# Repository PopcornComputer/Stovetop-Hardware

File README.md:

# Stovetop Hardware
[![CC BY-NC-SA 4.0][cc-by-nc-sa-shield]][cc-by-nc-sa]
[![Follow Source Parts on Twitter][twitter-follow-shield]][twitter-follow]
[![Subscribe to Source Parts' Subreddit][reddit-subscribers-shield]][sourceparts-subreddit]

## Purchase
**Stovetop™** is available for purchase in our webstore: [https://shop.popcorncomputer.com/products/stovetop][webstore]

## Documentation
To view the documentation for **Stovetop™** please visit: [https://docs.popcorncomputer.com/Stovetop][stovetop-docs]

If you have done something cool with **Stovetop™** or feel that something is missing from the documentation, please feel free to open an issue in the [documentation repository][documentation-repo] or submit a Pull Request in that repository. The source files for our documentation website can be found in the /docs folder in the [documentation repository][documentation-repo].

## License & Copyright
This work is licensed under a
[Creative Commons Attribution-NonCommercial-ShareAlike 4.0 International License][cc-by-nc-sa].

[![CC BY-NC-SA 4.0][cc-by-nc-sa-image]][cc-by-nc-sa]

Source Parts Inc. © 2022

**Stovetop™** is a trademark of Source Parts Inc.

[cc-by-nc-sa]: http://creativecommons.org/licenses/by-nc-sa/4.0/
[cc-by-nc-sa-image]: https://licensebuttons.net/l/by-nc-sa/4.0/88x31.png
[cc-by-nc-sa-shield]: https://img.shields.io/badge/License-CC%20BY--NC--SA%204.0-lightgrey.svg
[twitter-follow]: https://twitter.com/intent/follow?screen_name=sourceparts
[twitter-follow-shield]: https://img.shields.io/twitter/follow/sourceparts?style=social&logo=twitter
[sourceparts-subreddit]: https://reddit.com/r/sourceparts
[reddit-subscribers-shield]: https://img.shields.io/reddit/subreddit-subscribers/sourceparts?style=social
[stovetop-docs]: https://docs.popcorncomputer.com/Stovetop
[webstore]: https://shop.popcorncomputer.com/products/stovetop
[documentation-repo]: https://github.com/PopcornComputer/Stovetop

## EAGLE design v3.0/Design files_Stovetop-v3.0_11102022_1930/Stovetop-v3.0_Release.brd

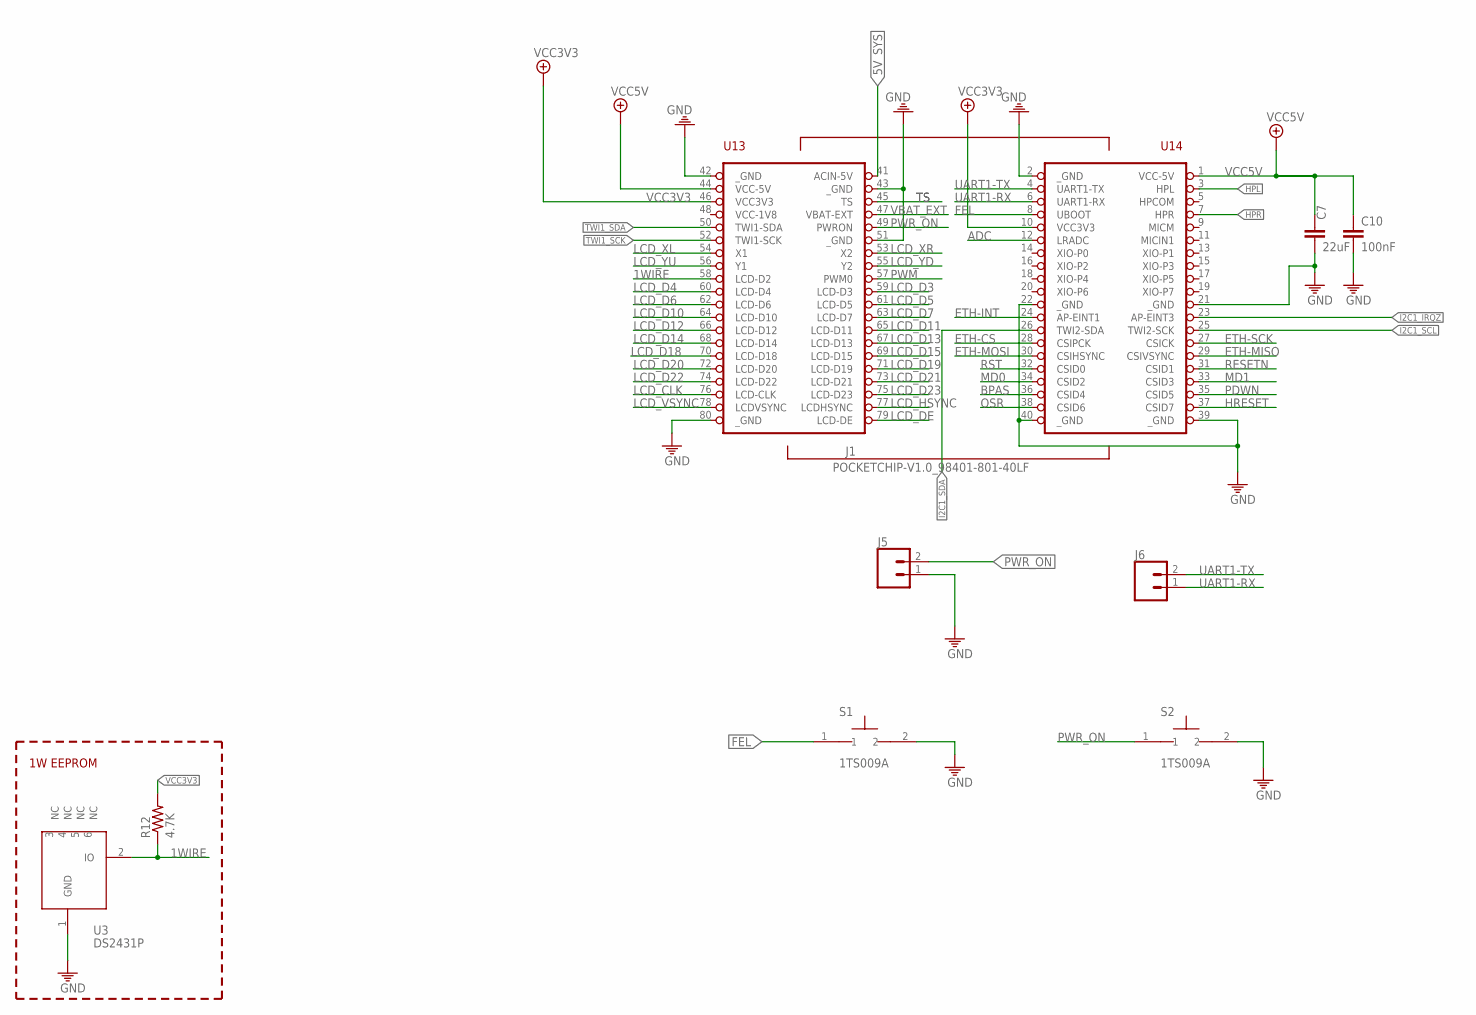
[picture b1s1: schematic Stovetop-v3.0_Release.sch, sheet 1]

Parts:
C7: 22uF; C1206
C10: 100nF; C0402
J1: POCKETCHIP-V1.0_98401-801-40LF
J5, J6: CONN_02LOCK; 1X02_LOCK
R12: 4.7K; R0402
S1, S2: 1TS009A
U3: DS2431P; TSOC6

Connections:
1WIRE: J1.58 (LCD-D2), R12.1, U3.2 (IO)
5V_SYS: J1.41 (ACIN-5V); also elsewhere on the board
ADC: J1.12 (LRADC)
BPAS: J1.36 (CSID4); also elsewhere on the board
ETH-CS: J1.28 (CSIPCK); also elsewhere on the board
ETH-INT: J1.24 (AP-EINT1); also elsewhere on the board
ETH-MISO: J1.29 (CSIVSYNC); also elsewhere on the board
ETH-MOSI: J1.30 (CSIHSYNC); also elsewhere on the board
ETH-SCK: J1.27 (CSICK); also elsewhere on the board
FEL: J1.8 (UBOOT), S1.1
GND: C7.2, C10.2, J1.2 (_GND), J1.21 (_GND), J1.22 (_GND), J1.39 (_GND), J1.40 (_GND), J1.42 (_GND), J1.43 (_GND), J1.51 (_GND), J1.80 (_GND), J5.1, S1.2, S2.2, U3.1 (GND); also elsewhere on the board
HPL: J1.3 (HPL); also elsewhere on the board
HPR: J1.7 (HPR); also elsewhere on the board
HRESET: J1.37 (CSID7); also elsewhere on the board
I2C1_IRQZ: J1.23 (AP-EINT3); also elsewhere on the board
I2C1_SCL: J1.25 (TWI2-SCK); also elsewhere on the board
I2C1_SDA: J1.26 (TWI2-SDA); also elsewhere on the board
LCD_CLK: J1.76 (LCD-CLK); also elsewhere on the board
LCD_D3: J1.59 (LCD-D3); also elsewhere on the board
LCD_D4: J1.60 (LCD-D4); also elsewhere on the board
LCD_D5: J1.61 (LCD-D5); also elsewhere on the board
LCD_D6: J1.62 (LCD-D6); also elsewhere on the board
LCD_D7: J1.63 (LCD-D7); also elsewhere on the board
LCD_D10: J1.64 (LCD-D10); also elsewhere on the board
LCD_D11: J1.65 (LCD-D11); also elsewhere on the board
LCD_D12: J1.66 (LCD-D12); also elsewhere on the board
LCD_D13: J1.67 (LCD-D13); also elsewhere on the board
LCD_D14: J1.68 (LCD-D14); also elsewhere on the board
LCD_D15: J1.69 (LCD-D15); also elsewhere on the board
LCD_D18: J1.70 (LCD-D18); also elsewhere on the board
LCD_D19: J1.71 (LCD-D19); also elsewhere on the board
LCD_D20: J1.72 (LCD-D20); also elsewhere on the board
LCD_D21: J1.73 (LCD-D21); also elsewhere on the board
LCD_D22: J1.74 (LCD-D22); also elsewhere on the board
LCD_D23: J1.75 (LCD-D23); also elsewhere on the board
LCD_DE: J1.79 (LCD-DE); also elsewhere on the board
LCD_HSYNC: J1.77 (LCDHSYNC); also elsewhere on the board
LCD_VSYNC: J1.78 (LCDVSYNC); also elsewhere on the board
LCD_XL: J1.54 (X1)
LCD_XR: J1.53 (X2)
LCD_YD: J1.55 (Y2)
LCD_YU: J1.56 (Y1)
MD0: J1.34 (CSID2); also elsewhere on the board
MD1: J1.33 (CSID3); also elsewhere on the board
OSR: J1.38 (CSID6); also elsewhere on the board
PDWN: J1.35 (CSID5); also elsewhere on the board
PWM: J1.57 (PWM0)
PWR_ON: J1.49 (PWRON), J5.2, S2.1
RESETN: J1.31 (CSID1)
RST: J1.32 (CSID0); also elsewhere on the board
TS: J1.45 (TS)
TWI1_SCK: J1.52 (TWI1-SCK); also elsewhere on the board
TWI1_SDA: J1.50 (TWI1-SDA); also elsewhere on the board
UART1-RX: J1.6 (UART1-RX), J6.1; also elsewhere on the board
UART1-TX: J1.4 (UART1-TX), J6.2; also elsewhere on the board
VBAT_EXT: J1.47 (VBAT-EXT)
VCC3V3: J1.10 (VCC3V3), J1.46 (VCC3V3), R12.2; also elsewhere on the board
VCC5V: C7.1, C10.1, J1.1 (VCC-5V), J1.44 (VCC-5V); also elsewhere on the board

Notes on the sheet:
1W EEPROM

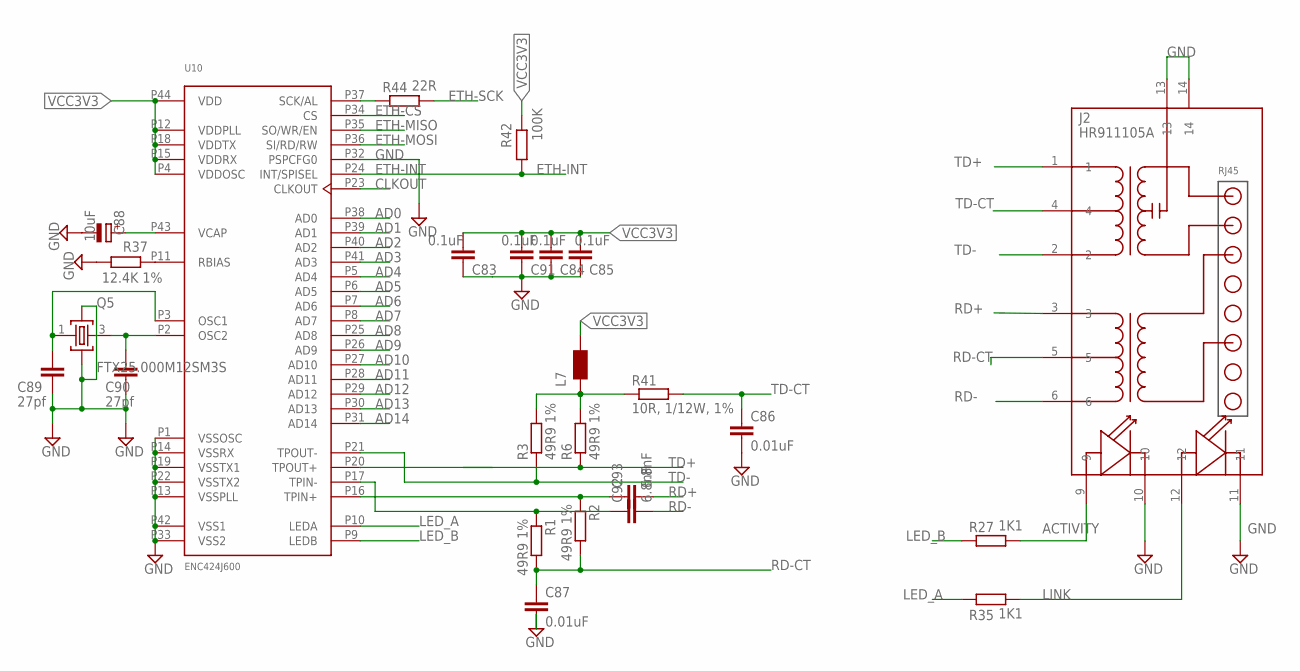
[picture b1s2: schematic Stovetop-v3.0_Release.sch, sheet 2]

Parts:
C83, C84, C85, C91: 0.1uF; C0603
C86, C87: 0.01uF; C0603
C88: 10uF; SMC_A
C89, C90: 27pf; C0603
C92, C93: 6.8nF; C0603
J2: HR911105A
L7: WE-KIL_0805; WE-KI_0805_B
Q5: FTX25.000M12SM3S; CRISTALLI_CRYSTAL3.2X2.5
R1, R2, R3, R6: 49R9 1%; R0603
R27, R35: 1K1; R0603
R37: 12.4K 1%; R0603
R41: 10R, 1/12W, 1%; R0603
R42: 100K; R0603
R44: 22R; R0603
U10: ENC424J600; TQFP44

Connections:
ACTIVITY: J2.9, R27.2
AD0: U10.P38 (AD0)
AD1: U10.P39 (AD1)
AD2: U10.P40 (AD2)
AD3: U10.P41 (AD3)
AD4: U10.P5 (AD4)
AD5: U10.P6 (AD5)
AD6: U10.P7 (AD6)
AD7: U10.P8 (AD7)
AD8: U10.P25 (AD8)
AD9: U10.P26 (AD9)
AD10: U10.P27 (AD10)
AD11: U10.P28 (AD11)
AD12: U10.P29 (AD12)
AD13: U10.P30 (AD13)
AD14: U10.P31 (AD14)
CCT: L7.2 (1), R3.2, R6.2, R41.1
CLKOUT: U10.P23 (CLKOUT)
DSFGDF: C92.1, R1.1, U10.P17 (TPIN-)
DSGDFSG: C93.1, R2.1, U10.P16 (TPIN+)
ETH-CS: U10.P34 (CS); also elsewhere on the board
ETH-INT: R42.2, U10.P24 (INT/SPISEL); also elsewhere on the board
ETH-MISO: U10.P35 (SO/WR/EN); also elsewhere on the board
ETH-MOSI: U10.P36 (SI/RD/RW); also elsewhere on the board
ETH-SCK: R44.2; also elsewhere on the board
GND: C83.2, C84.2, C85.2, C86.2, C87.2, C88.-, C89.2, C90.2, C91.2, J2.10, J2.11, J2.13, J2.14, Q5.2, Q5.4, R37.2, U10.P1 (VSSOSC), U10.P13 (VSSPLL), U10.P14 (VSSRX), U10.P19 (VSSTX1), U10.P22 (VSSTX2), U10.P32 (PSPCFG0), U10.P33 (VSS2), U10.P42 (VSS1); also elsewhere on the board
LED_A: R35.1, U10.P10 (LEDA)
LED_B: R27.1, U10.P9 (LEDB)
LINK: J2.12, R35.2
unnamed: R44.1, U10.P37 (SCK/AL)
unnamed: C88.+, U10.P43 (VCAP)
unnamed: R37.1, U10.P11 (RBIAS)
unnamed: C89.1, Q5.1, U10.P3 (OSC1)
unnamed: C90.1, Q5.3, U10.P2 (OSC2)
RD+: C93.2, J2.3
RD-: C92.2, J2.6
RD-CT: C87.1, J2.5, R1.2, R2.2
TD+: J2.1, R6.1, U10.P20 (TPOUT+)
TD-: J2.2, R3.1, U10.P21 (TPOUT-)
TD-CT: C86.1, J2.4, R41.2
VCC3V3: C83.1, C84.1, C85.1, C91.1, L7.1 (2), R42.1, U10.P4 (VDDOSC), U10.P12 (VDDPLL), U10.P15 (VDDRX), U10.P18 (VDDTX), U10.P44 (VDD); also elsewhere on the board

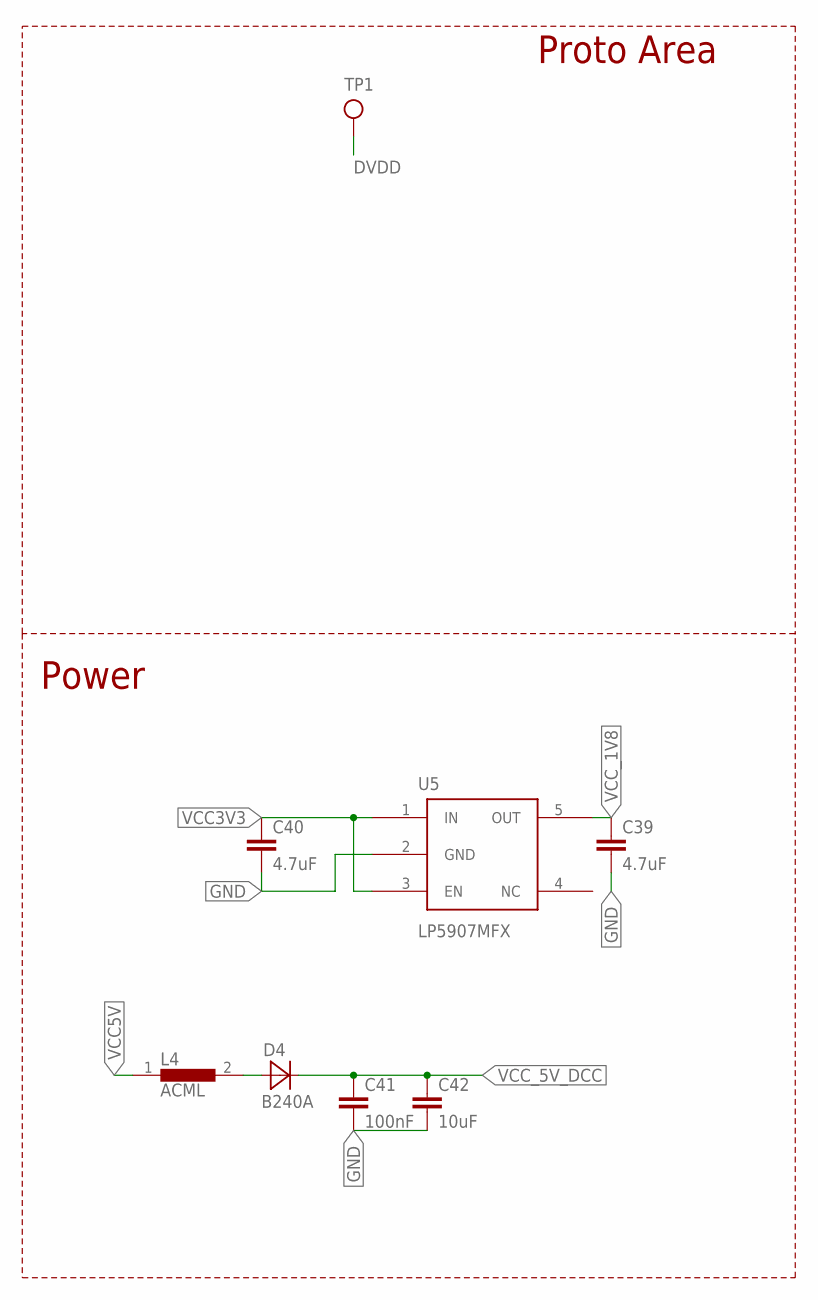
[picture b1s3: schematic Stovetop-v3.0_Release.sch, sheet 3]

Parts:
C39, C40: 4.7uF; 1608_0603
C41: 100nF; 1608_0603
C42: 10uF; 1608_0603
D4: B240A; SMA
L4: ACML; 0603
TP1: CHIP_HDMI_TEST_POINT; CHIP_HDMI_TP-1MMX1MM
U5: LP5907MFX; SOT23-5

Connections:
DVDD: TP1.0; also elsewhere on the board
GND: C39.2, C40.2, C41.2, C42.2, U5.2 (GND); also elsewhere on the board
unnamed: D4.1 (A), L4.2
VCC3V3: C40.1, U5.1 (IN), U5.3 (EN); also elsewhere on the board
VCC5V: L4.1; also elsewhere on the board
VCC_1V8: C39.1, U5.5 (OUT); also elsewhere on the board
VCC_5V_DCC: C41.1, C42.1, D4.2 (C); also elsewhere on the board

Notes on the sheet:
Proto Area
Power

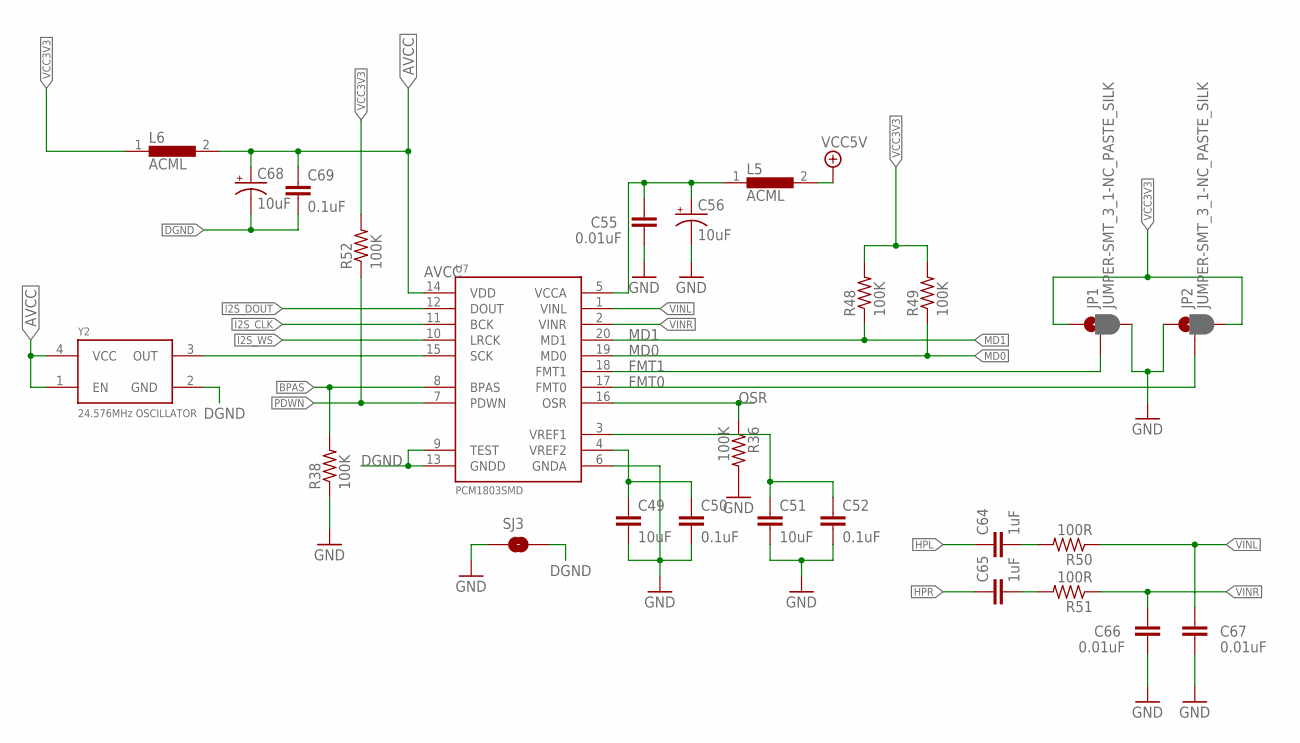
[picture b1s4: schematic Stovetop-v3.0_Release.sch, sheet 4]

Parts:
C49, C51: 10uF; 0603
C50, C52, C69: 0.1uF; 0402-CAP
C55, C66, C67: 0.01uF; 0402-CAP
C56, C68: 10uF; EIA3216
C64, C65: 1uF; 0402-CAP
JP1, JP2: JUMPER-SMT_3_1-NC_PASTE_SILK; SMT-JUMPER_3_1-NC_PASTE_SILK
L5, L6: ACML; 0603
R36, R38, R48, R49, R52: 100K; J1-0603
R50, R51: 100R; J1-0603
SJ3: SPARKFUN_SOLDERJUMPERTRACE; SPARKFUN_SJ_2S-TRACE
U7: PCM1803SMD; SSOP20
Y2: 24.576MHz OSCILLATOR; CRYSTAL-SMD-7.5X5.2-6PIN

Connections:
AVCC: C68.A (+), C69.1, L6.2, U7.14 (VDD), Y2.1 (EN), Y2.4 (VCC)
BPAS: R38.2, U7.8 (BPAS); also elsewhere on the board
DGND: C68.C (-), C69.2, SJ3.2, U7.9 (TEST), U7.13 (GNDD), Y2.2 (GND)
FMT0: JP2.2, U7.17 (FMT0)
FMT1: JP1.2, U7.18 (FMT1)
GND: C49.2, C50.2, C51.2, C52.2, C55.1, C56.C (-), C66.1, C67.1, JP1.3, JP2.1, R36.2, R38.1, SJ3.1, U7.6 (GNDA); also elsewhere on the board
HPL: C64.1; also elsewhere on the board
HPR: C65.1; also elsewhere on the board
I2S_CLK: U7.11 (BCK); also elsewhere on the board
I2S_DOUT: U7.12 (DOUT); also elsewhere on the board
I2S_WS: U7.10 (LRCK); also elsewhere on the board
MD0: R49.1, U7.19 (MD0); also elsewhere on the board
MD1: R48.1, U7.20 (MD1); also elsewhere on the board
unnamed: C49.1, C50.1, U7.4 (VREF2)
unnamed: C51.1, C52.1, U7.3 (VREF1)
unnamed: U7.15 (SCK), Y2.3 (OUT)
unnamed: C55.2, C56.A (+), L5.1, U7.5 (VCCA)
unnamed: C64.2, R50.2
unnamed: C65.2, R51.2
OSR: R36.1, U7.16 (OSR); also elsewhere on the board
PDWN: R52.1, U7.7 (PDWN); also elsewhere on the board
VCC3V3: JP1.1, JP2.3, L6.1, R48.2, R49.2, R52.2; also elsewhere on the board
VCC5V: L5.2; also elsewhere on the board
VINL: C67.2, R50.1, U7.1 (VINL)
VINR: C66.2, R51.1, U7.2 (VINR)

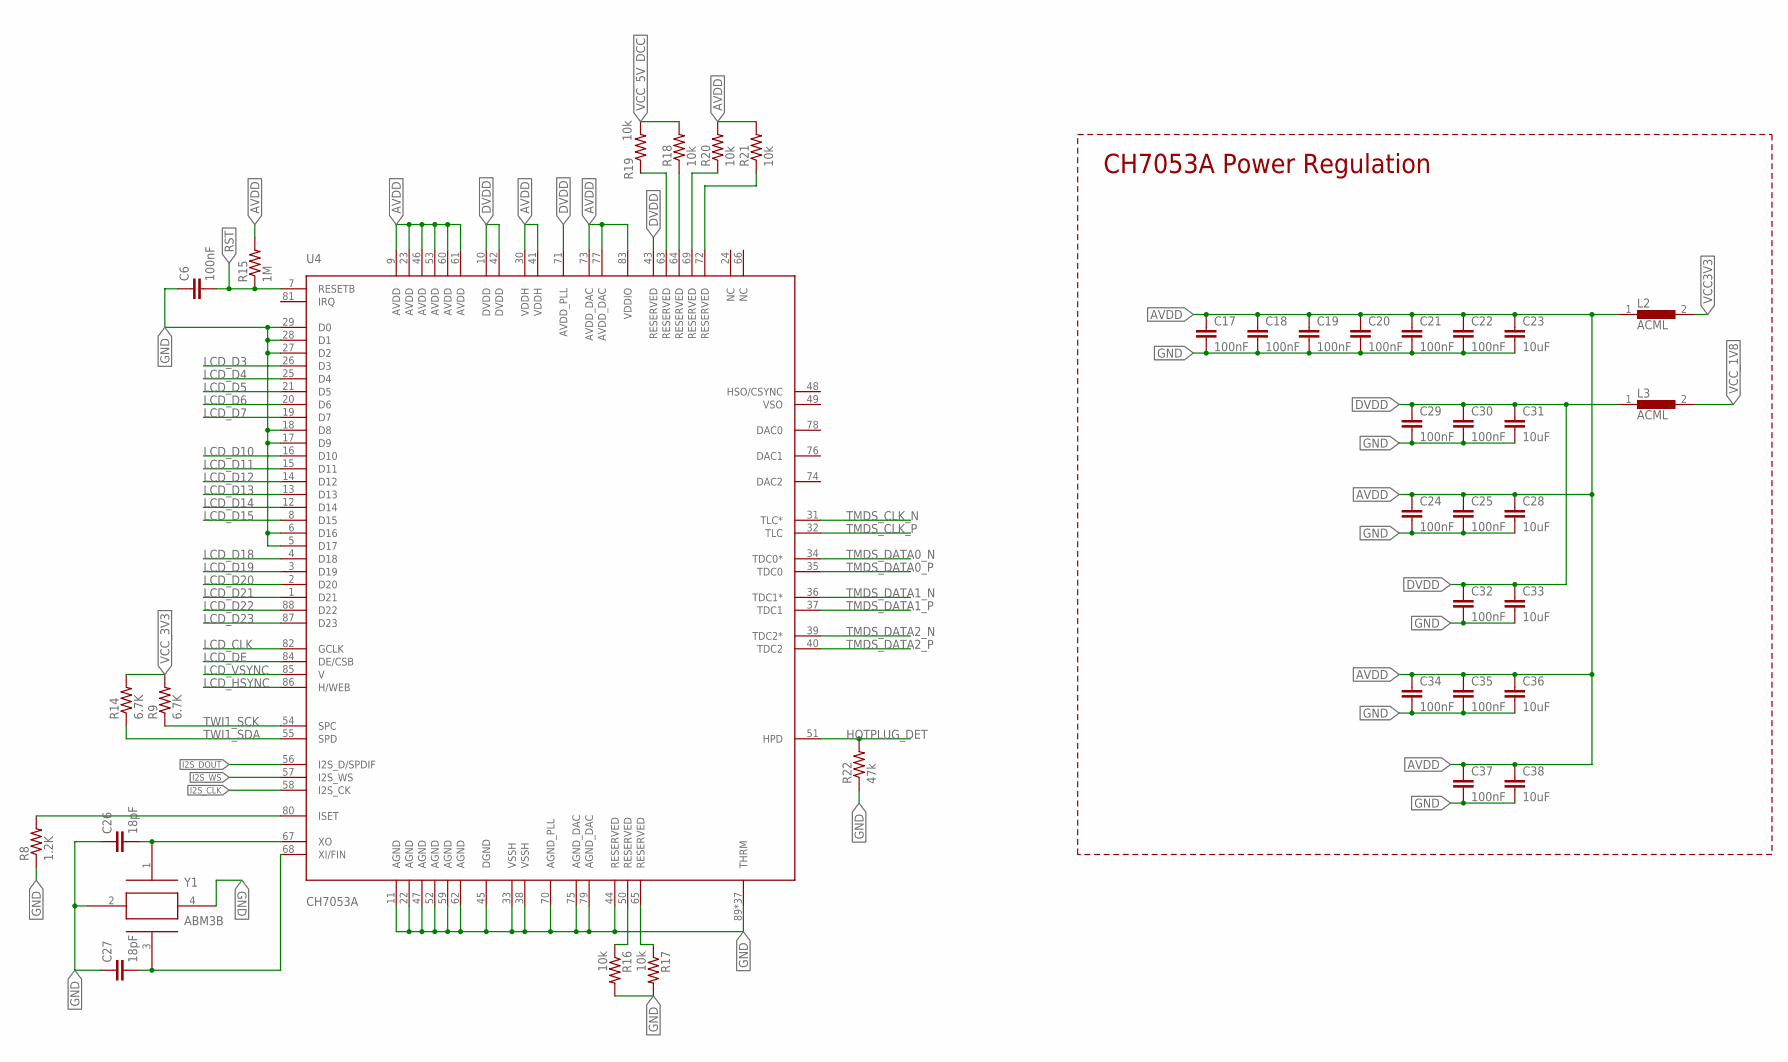
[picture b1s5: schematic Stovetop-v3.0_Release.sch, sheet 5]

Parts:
C6, C17, C18, C19, C20, C21, C22, C24, C25, C29, C30, C32, C34, C35, C37: 100nF; 1608_0603
C23, C28, C31, C33, C36, C38: 10uF; 1608_0603
C26, C27: 18pF; 1608_0603
L2, L3: ACML; 0603
R8: 1.2K; J1-0603
R9, R14: 6.7K; J1-0603
R15: 1M; J1-0603
R16, R17, R18, R19, R20, R21: 10k; J1-0603
R22: 47k; J1-0603
U4: CH7053A; QFN40P1000X1000X90_HS-89M
Y1: ABM3B

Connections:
AVDD: C17.1, C18.1, C19.1, C20.1, C21.1, C22.1, C23.1, C24.1, C25.1, C28.1, C34.1, C35.1, C36.1, C37.1, C38.1, L2.1, R15.2, R20.2, R21.2, U4.9 (AVDD), U4.23 (AVDD), U4.30 (VDDH), U4.41 (VDDH), U4.46 (AVDD), U4.53 (AVDD), U4.60 (AVDD), U4.61 (AVDD), U4.73 (AVDD_DAC), U4.77 (AVDD_DAC), U4.83 (VDDIO)
DVDD: C29.1, C30.1, C31.1, C32.1, C33.1, L3.1, U4.10 (DVDD), U4.42 (DVDD), U4.43 (RESERVED), U4.71 (AVDD_PLL); also elsewhere on the board
GND: C6.1, C17.2, C18.2, C19.2, C20.2, C21.2, C22.2, C23.2, C24.2, C25.2, C26.1, C27.1, C28.2, C29.2, C30.2, C31.2, C32.2, C33.2, C34.2, C35.2, C36.2, C37.2, C38.2, R8.1, R16.2, R17.2, R22.1, U4.5 (D17), U4.6 (D16), U4.11 (AGND), U4.17 (D9), U4.18 (D8), U4.22 (AGND), U4.27 (D2), U4.28 (D1), U4.29 (D0), U4.33 (VSSH), U4.38 (VSSH), U4.44 (RESERVED), U4.45 (DGND), U4.47 (AGND), U4.52 (AGND), U4.59 (AGND), U4.62 (AGND), U4.70 (AGND_PLL), U4.75 (AGND_DAC), U4.79 (AGND_DAC), U4.89 (THRM), U4.P$1 (THRM), U4.P$2 (THRM), U4.P$3 (THRM), U4.P$4 (THRM), U4.P$5 (THRM), U4.P$6 (THRM), U4.P$7 (THRM), U4.P$8 (THRM), U4.P$9 (THRM), U4.P$10 (THRM), U4.P$11 (THRM), U4.P$12 (THRM), U4.P$13 (THRM), U4.P$14 (THRM), U4.P$15 (THRM), U4.P$16 (THRM), U4.P$17 (THRM), U4.P$18 (THRM), U4.P$19 (THRM), U4.P$20 (THRM), U4.P$21 (THRM), U4.P$22 (THRM), U4.P$23 (THRM), U4.P$24 (THRM), U4.P$25 (THRM), U4.P$26 (THRM), U4.P$27 (THRM), U4.P$28 (THRM), U4.P$29 (THRM), U4.P$30 (THRM), U4.P$31 (THRM), U4.P$32 (THRM), U4.P$33 (THRM), U4.P$34 (THRM), U4.P$35 (THRM), U4.P$36 (THRM), Y1.2, Y1.4; also elsewhere on the board
HOTPLUG_DET: R22.2, U4.51 (HPD); also elsewhere on the board
I2S_CLK: U4.58 (I2S_CK); also elsewhere on the board
I2S_DOUT: U4.56 (I2S_D/SPDIF); also elsewhere on the board
I2S_WS: U4.57 (I2S_WS); also elsewhere on the board
LCD_CLK: U4.82 (GCLK); also elsewhere on the board
LCD_D3: U4.26 (D3); also elsewhere on the board
LCD_D4: U4.25 (D4); also elsewhere on the board
LCD_D5: U4.21 (D5); also elsewhere on the board
LCD_D6: U4.20 (D6); also elsewhere on the board
LCD_D7: U4.19 (D7); also elsewhere on the board
LCD_D10: U4.16 (D10); also elsewhere on the board
LCD_D11: U4.15 (D11); also elsewhere on the board
LCD_D12: U4.14 (D12); also elsewhere on the board
LCD_D13: U4.13 (D13); also elsewhere on the board
LCD_D14: U4.12 (D14); also elsewhere on the board
LCD_D15: U4.8 (D15); also elsewhere on the board
LCD_D18: U4.4 (D18); also elsewhere on the board
LCD_D19: U4.3 (D19); also elsewhere on the board
LCD_D20: U4.2 (D20); also elsewhere on the board
LCD_D21: U4.1 (D21); also elsewhere on the board
LCD_D22: U4.88 (D22); also elsewhere on the board
LCD_D23: U4.87 (D23); also elsewhere on the board
LCD_DE: U4.84 (DE/CSB); also elsewhere on the board
LCD_HSYNC: U4.86 (H/WEB); also elsewhere on the board
LCD_VSYNC: U4.85 (V); also elsewhere on the board
unnamed: C27.2, U4.68 (XI/FIN), Y1.3
unnamed: R8.2, U4.80 (ISET)
unnamed: R16.1, U4.50 (RESERVED)
unnamed: R17.1, U4.65 (RESERVED)
unnamed: R19.1, U4.63 (RESERVED)
unnamed: R18.1, U4.64 (RESERVED)
unnamed: R21.1, U4.72 (RESERVED)
unnamed: R20.1, U4.69 (RESERVED)
unnamed: C26.2, U4.67 (XO), Y1.1
RST: C6.2, R15.1, U4.7 (RESETB); also elsewhere on the board
TMDS_CLK_N: U4.31 (TLC*); also elsewhere on the board
TMDS_CLK_P: U4.32 (TLC); also elsewhere on the board
TMDS_DATA0_N: U4.34 (TDC0*); also elsewhere on the board
TMDS_DATA0_P: U4.35 (TDC0); also elsewhere on the board
TMDS_DATA1_N: U4.36 (TDC1*); also elsewhere on the board
TMDS_DATA1_P: U4.37 (TDC1); also elsewhere on the board
TMDS_DATA2_N: U4.39 (TDC2*); also elsewhere on the board
TMDS_DATA2_P: U4.40 (TDC2); also elsewhere on the board
TWI1_SCK: R9.1, U4.54 (SPC); also elsewhere on the board
TWI1_SDA: R14.1, U4.55 (SPD); also elsewhere on the board
VCC3V3: L2.2; also elsewhere on the board
VCC_1V8: L3.2; also elsewhere on the board
VCC_3V3: R9.2, R14.2
VCC_5V_DCC: R18.2, R19.2; also elsewhere on the board

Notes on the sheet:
CH7053A Power Regulation

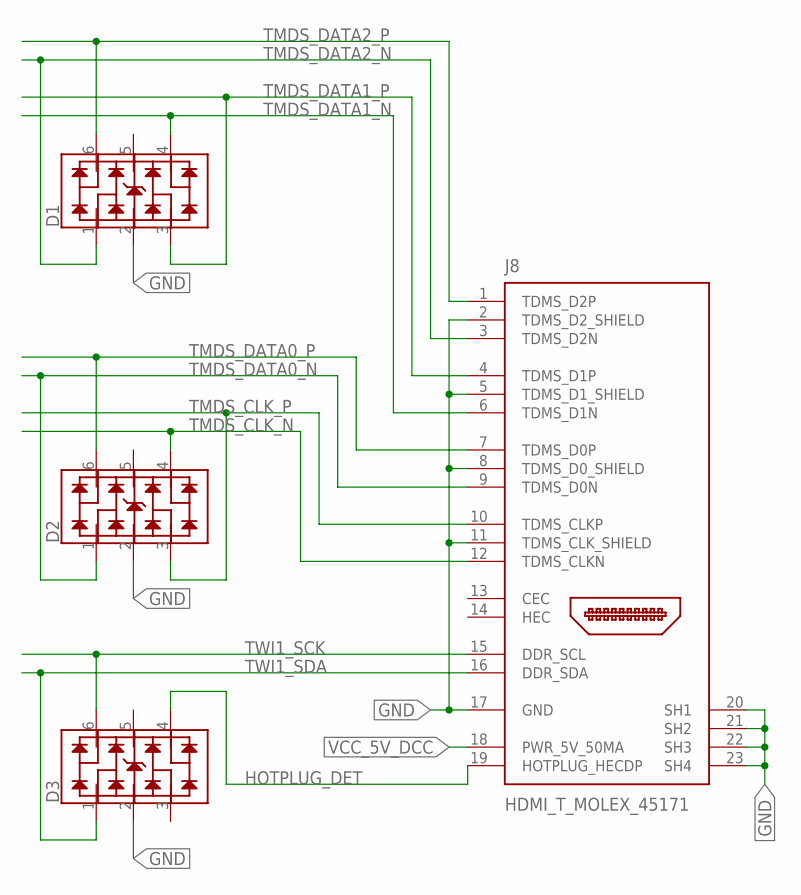
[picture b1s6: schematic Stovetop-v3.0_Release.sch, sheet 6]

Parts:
D1, D2, D3: D-SEMTECH-RCLAMP0504S; T_SOT95P285X90-6N
J8: HDMI_T_MOLEX_45171; CHIP_HDMI_T_MOLEX_45171

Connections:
GND: D1.2, D2.2, D3.2, J8.2 (TDMS_D2_SHIELD), J8.5 (TDMS_D1_SHIELD), J8.8 (TDMS_D0_SHIELD), J8.11 (TDMS_CLK_SHIELD), J8.17 (GND), J8.20 (SH1), J8.21 (SH2), J8.22 (SH3), J8.23 (SH4); also elsewhere on the board
HOTPLUG_DET: D3.4, J8.19 (HOTPLUG_HECDP); also elsewhere on the board
TMDS_CLK_N: D2.4, J8.12 (TDMS_CLKN); also elsewhere on the board
TMDS_CLK_P: D2.3, J8.10 (TDMS_CLKP); also elsewhere on the board
TMDS_DATA0_N: D2.1, J8.9 (TDMS_D0N); also elsewhere on the board
TMDS_DATA0_P: D2.6, J8.7 (TDMS_D0P); also elsewhere on the board
TMDS_DATA1_N: D1.4, J8.6 (TDMS_D1N); also elsewhere on the board
TMDS_DATA1_P: D1.3, J8.4 (TDMS_D1P); also elsewhere on the board
TMDS_DATA2_N: D1.1, J8.3 (TDMS_D2N); also elsewhere on the board
TMDS_DATA2_P: D1.6, J8.1 (TDMS_D2P); also elsewhere on the board
TWI1_SCK: D3.6, J8.15 (DDR_SCL); also elsewhere on the board
TWI1_SDA: D3.1, J8.16 (DDR_SDA); also elsewhere on the board
VCC_5V_DCC: J8.18 (PWR_5V_50MA); also elsewhere on the board

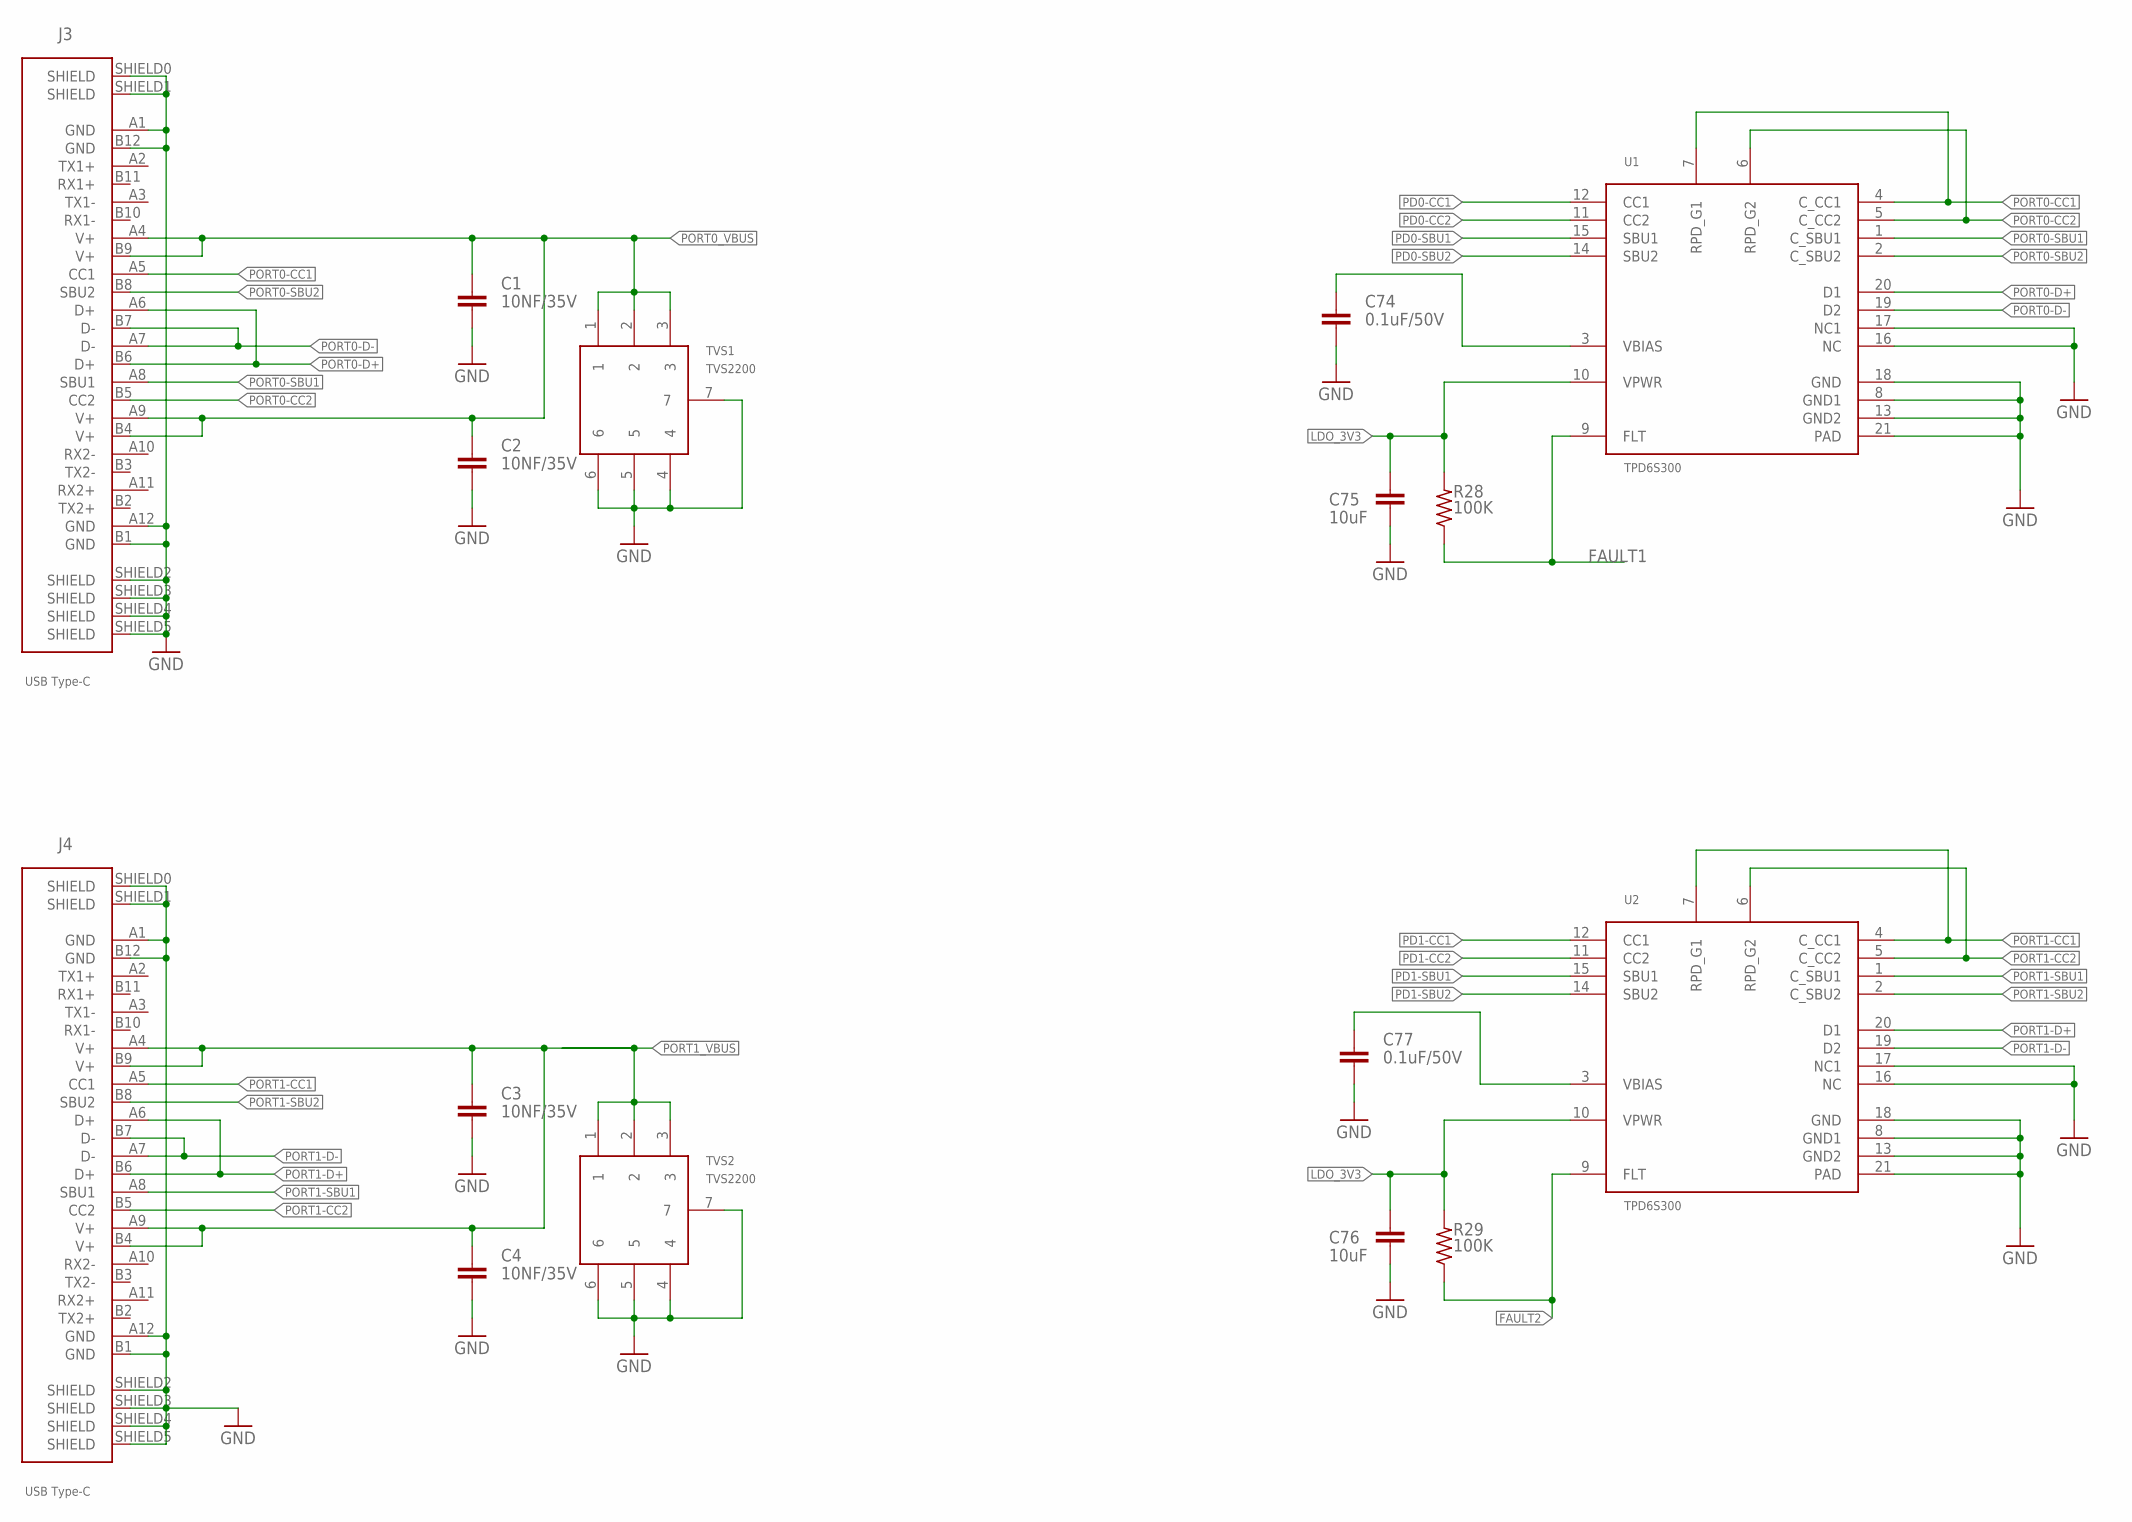
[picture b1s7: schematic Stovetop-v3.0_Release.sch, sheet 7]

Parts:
C1, C2, C3, C4: 10NF/35V; 0402-CAP
C74, C77: 0.1uF/50V; 0603-CAP
C75, C76: 10uF; 0603-CAP
J3, J4: STOVETOP-V2.0_03062020_1600_STOVETOP-V2.0_CHECK_T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; STOVETOP-V2.0_03062020_1600_STOVETOP-V2.0_CHECK_TRISTAN-ROB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
R28, R29: 100K; R0402
TVS1, TVS2: TVS2200
U1, U2: TPD6S300

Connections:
FAULT1: R28.1, U1.9 (FLT); also elsewhere on the board
FAULT2: R29.1, U2.9 (FLT); also elsewhere on the board
GND: C1.1, C2.1, C3.1, C4.1, C74.1, C75.1, C76.1, C77.1, J3.A1 (GND), J3.A12 (GND), J3.B1 (GND), J3.B12 (GND), J3.SHIELD0 (SHIELD), J3.SHIELD1 (SHIELD), J3.SHIELD2 (SHIELD), J3.SHIELD3 (SHIELD), J3.SHIELD4 (SHIELD), J3.SHIELD5 (SHIELD), J4.A1 (GND), J4.A12 (GND), J4.B1 (GND), J4.B12 (GND), J4.SHIELD0 (SHIELD), J4.SHIELD1 (SHIELD), J4.SHIELD2 (SHIELD), J4.SHIELD3 (SHIELD), J4.SHIELD4 (SHIELD), J4.SHIELD5 (SHIELD), TVS1.4, TVS1.5, TVS1.6, TVS1.7, TVS2.4, TVS2.5, TVS2.6, TVS2.7, U1.8 (GND1), U1.13 (GND2), U1.16 (NC), U1.17 (NC1), U1.18 (GND), U1.21 (PAD), U2.8 (GND1), U2.13 (GND2), U2.16 (NC), U2.17 (NC1), U2.18 (GND), U2.21 (PAD); also elsewhere on the board
LDO_3V3: C75.2, C76.2, R28.2, R29.2, U1.10 (VPWR), U2.10 (VPWR); also elsewhere on the board
unnamed: C74.2, U1.3 (VBIAS)
unnamed: C77.2, U2.3 (VBIAS)
PD0-CC1: U1.12 (CC1); also elsewhere on the board
PD0-CC2: U1.11 (CC2); also elsewhere on the board
PD0-SBU1: U1.15 (SBU1)
PD0-SBU2: U1.14 (SBU2)
PD1-CC1: U2.12 (CC1); also elsewhere on the board
PD1-CC2: U2.11 (CC2); also elsewhere on the board
PD1-SBU1: U2.15 (SBU1)
PD1-SBU2: U2.14 (SBU2)
PORT0-CC1: J3.A5 (CC1), U1.4 (C_CC1), U1.7 (RPD_G1)
PORT0-CC2: J3.B5 (CC2), U1.5 (C_CC2), U1.6 (RPD_G2)
PORT0-D+: J3.A6 (D+), J3.B6 (D+), U1.20 (D1); also elsewhere on the board
PORT0-D-: J3.A7 (D-), J3.B7 (D-), U1.19 (D2); also elsewhere on the board
PORT0-SBU1: J3.A8 (SBU1), U1.1 (C_SBU1)
PORT0-SBU2: J3.B8 (SBU2), U1.2 (C_SBU2)
PORT0_VBUS: C1.2, C2.2, J3.A4 (V+), J3.A9 (V+), J3.B4 (V+), J3.B9 (V+), TVS1.1, TVS1.2, TVS1.3; also elsewhere on the board
PORT1-CC1: J4.A5 (CC1), U2.4 (C_CC1), U2.7 (RPD_G1)
PORT1-CC2: J4.B5 (CC2), U2.5 (C_CC2), U2.6 (RPD_G2)
PORT1-D+: J4.A6 (D+), J4.B6 (D+), U2.20 (D1); also elsewhere on the board
PORT1-D-: J4.A7 (D-), J4.B7 (D-), U2.19 (D2); also elsewhere on the board
PORT1-SBU1: J4.A8 (SBU1), U2.1 (C_SBU1)
PORT1-SBU2: J4.B8 (SBU2), U2.2 (C_SBU2)
PORT1_VBUS: C3.2, C4.2, J4.A4 (V+), J4.A9 (V+), J4.B4 (V+), J4.B9 (V+), TVS2.1, TVS2.2, TVS2.3; also elsewhere on the board

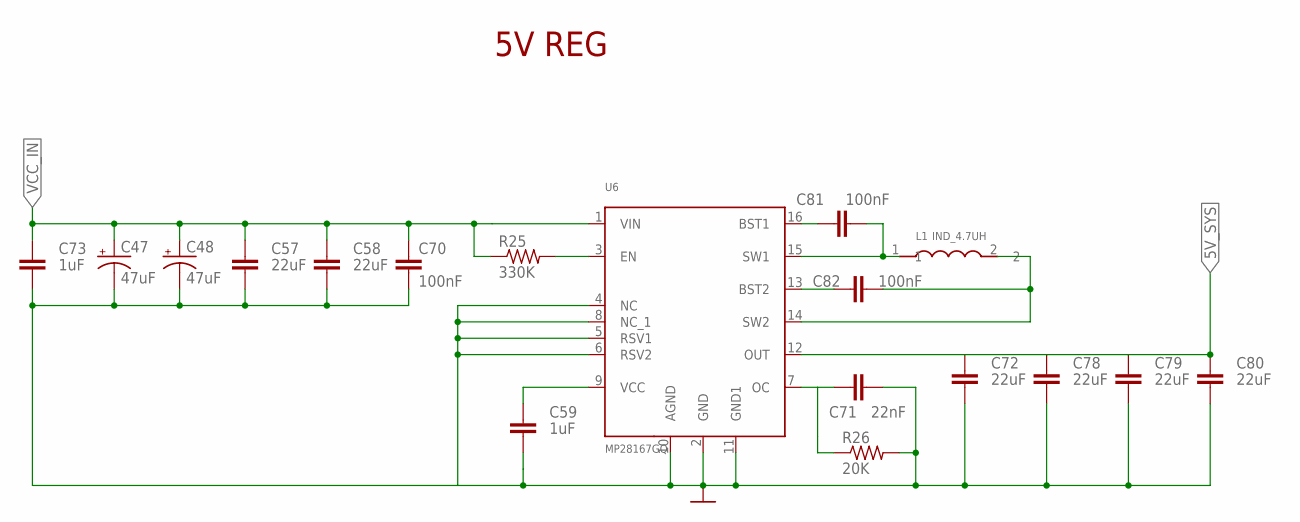
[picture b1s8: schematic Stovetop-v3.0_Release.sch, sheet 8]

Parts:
C47, C48: 47uF; D/7343-31W
C57, C58, C72, C78, C79, C80: 22uF; 0805
C59, C73: 1uF; 0805
C70, C81, C82: 100nF; C0402
C71: 22nF; 0805
L1: IND_4.7UH
R25: 330K; R0402
R26: 20K; R0603
U6: MP28167GQ

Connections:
5V_SYS: C72.2, C78.2, C79.2, C80.2, U6.12 (OUT); also elsewhere on the board
GND: C47.-, C48.-, C57.1, C58.1, C59.1, C70.2, C71.1, C72.1, C73.1, C78.1, C79.1, C80.1, R26.2, U6.2 (GND), U6.4 (NC), U6.5 (RSV1), U6.6 (RSV2), U6.8 (NC_1), U6.10 (AGND), U6.11 (GND1); also elsewhere on the board
unnamed: C71.2, R26.1, U6.7 (OC)
unnamed: R25.2, U6.3 (EN)
unnamed: C59.2, U6.9 (VCC)
unnamed: C81.1, U6.16 (BST1)
unnamed: C81.2, L1.1, U6.15 (SW1)
unnamed: C82.1, U6.13 (BST2)
unnamed: C82.2, L1.2, U6.14 (SW2)
VCC_IN: C47.+, C48.+, C57.2, C58.2, C70.1, C73.2, R25.1, U6.1 (VIN); also elsewhere on the board

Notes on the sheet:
5V REG

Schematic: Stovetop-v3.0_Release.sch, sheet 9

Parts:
C60: 0.1uF; C0402
C61: 10uF; C0402
C62, C63: 47pF; C0402
JP4, JP5: JUMPER-PAD-2-NC_BY_TRACE; PAD-JUMPER-2-NC_BY_TRACE_YES_SILK
R39, R40: 1K; R0402
R45: 0; R0402
R46, R47: 27R; R0402
RX_LED: Blue; LED-805
TX_LED: Amber; LED-805
UN0: FT230XS; SSOP-16

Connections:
5V_SYS: C61.1, UN0.12 (VCC); also elsewhere on the board
GND: C60.2, C61.2, C62.2, C63.2, R45.1, UN0.5 (GND), UN0.13 (GND); also elsewhere on the board
unnamed: R47.1, UN0.9 (USBDM)
unnamed: R46.1, UN0.8 (USBDP)
unnamed: R45.2, UN0.16 (CBUS3)
unnamed: R39.2, RX_LED.A
unnamed: R40.2, TX_LED.A
PORT1-D+: C62.1, R46.2; also elsewhere on the board
PORT1-D-: C63.1, R47.2; also elsewhere on the board
RXD: JP5.1, UN0.4 (RXD)
RXLED: RX_LED.C, UN0.7 (CBUS2)
TXD: JP4.1, UN0.1 (TXD)
TXLED: TX_LED.C, UN0.14 (CBUS1)
UART1-RX: JP4.2; also elsewhere on the board
UART1-TX: JP5.2; also elsewhere on the board
VCC3V3: R39.1, R40.1; also elsewhere on the board
VCCIO: C60.1, UN0.3 (VCCIO), UN0.10 (3V3OUT), UN0.11 (!RESET)

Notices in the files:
parts and their libraries:
SparkFun-Jumpers: Licensing: Creative Commons ShareAlike 4.0 International - https://creativecommons.org/licenses/by-sa/4.0
